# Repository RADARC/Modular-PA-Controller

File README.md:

# Modular-PA-Controller
Controller for High Power RF Power Amplifiers based Raspberry Pi Pico

Reading and District Amateur Radio Club(RADARC) are working together on a number of collaborative construction projects. This one is to design and build a Modular PA controller for High Power (1kW plus) semiconductor Power amplifiers.
This prototype implementation is targetted on the High Power HF PA Modules from [W6PQL](https://www.w6pql.com/) :

* [Kilowatt PA](https://www.w6pql.com/1_kw_sspa_for_1_8-54_mhz.htm)
* [LPF Filter](https://www.w6pql.com/a_1.5kw_lpf_for_160-6m.htm)
* [Directional Coupler](https://www.w6pql.com/1_8_to_54_mhz_dual_coupler.htm)

## Objectives:
<ul>
<li><strong>Protection</strong></li>
<ul>
<li>Protection of user and premises</li>
<li>Protection of Power Amplifier</li>
<li>Protection of connected equipment</li>
</ul>
<li><strong>Automatic Operation and Sequencing</strong>
<ul>
<li>Monitoring of Power Amplifier operational state</li>
<li>Control of operational components of Power Amplifier</li>
<li>Detection of state of connected equipment</li>
<li>Sequencing and crystal controlled timing of sequencing</li>
</ul>
<li><strong>Power Supplies</strong></li>
<ul>
<li>Low voltage power supplies derived from High Voltage PA supply</li>
<li>Variable Vgg Bias voltage supply</li>
</ul>
<li><strong> External control and Monitoring</strong></li>
<ul>
<li>LCD Display</li>
<li>USB</li>
<li>TTL Serial</li>
<li>Wifi and Bluetooth</li>

</ul>
</ul>

## Specification
<ul>
<li>Processor: Raspberry Pi Pico</li>
<li>Maximum input Voltage: 72V DC</li>
<li>Maximum switched PA current: 50A</li>
<li>Vgg bias output range: 1.4V to 4.7V</li>
<li>Number of PWM and RPM monitored fans(5V or 12V): 3</li>
<li>Number of voltage controlled fans: 1</li>
<li>Number of directional coupler inputs: 3</li>
<li>Analogue meter outputs: 2
<li>Transceiver ALC output: -12V to +12V</li>
<li>Transceiver digital SEND in/out Ports: 1</li>
<li>OLED control ports: 1</li>
<li>Rotary Encoders: 2</li>
<li>OLED control ports: 1</li>
<li>Input frequency measurement range: 100kHz to 50MHz</li>
<li>Input Power detection: 10dBm to 50dBm</li>
<li>Maximum input Power Tx/RX switching: 50dBm</li>
<li>Output TX/RX relay drivers(5V or 12V): 2</li>
<li>Output LPF relay drivers(%V or 12V): 6</li>
<li>I2C ports: 1</li>
<li>TTLserial ports: 1</li>                                                                                               
</ul>

## Hardware Implementation

The Modular PA Controller Is built around four PCB assemblies:

### Power Supply and Control Board
This board manages the high DC voltage (up to 72V) part of the PA controller. It provides switching of the DC supply up to 50A, also current monitoring and Voltage monitoring. The DC supply switching uses a watchdog an requires the processor to signal the switch every 500uS to keep the power on.
It derives two lower voltage power supplies at 12V 2A and 5V 1A. The 3.3V logic supply for th PA controller is provided by the regulator on the Pi Pico on the processor board.To control the Vgg Bias to the Power Amplifier Modules the board provides either a switched 12V supply to a regulator on the Power Amplifier Board, and also a variable voltage software controlled DC output.
All control and monitoring is via I2C control from the Processor Board.

[Kicad Files](./Kicad/PA_Power_V1/)

### Processor and Interface Board
This board contains the Raspberry Pi Pico microcontroller module. The module alo provides the 3.3V logic supply and the USB interface. Pi Pico modules with Bluetooth and Wi-fi may be used, also the higher performance RP2350 version.

[Pi Pico Data sheet](https://datasheets.raspberrypi.com/pico/pico-datasheet.pdf)

The board has two I2C buses. The internal bus connects to the on board ADC and DAC devices. The external I2C bus connects to the Power Supply and Control board(s), the Relay Driver board(s), LM75 temperature sensors, I2C OLED display, etc.

The board has an input TX/RX relay to bypass the Power Amplifier Modules as required.

### Relay Driver Board

### RF screen

## Software Implementation

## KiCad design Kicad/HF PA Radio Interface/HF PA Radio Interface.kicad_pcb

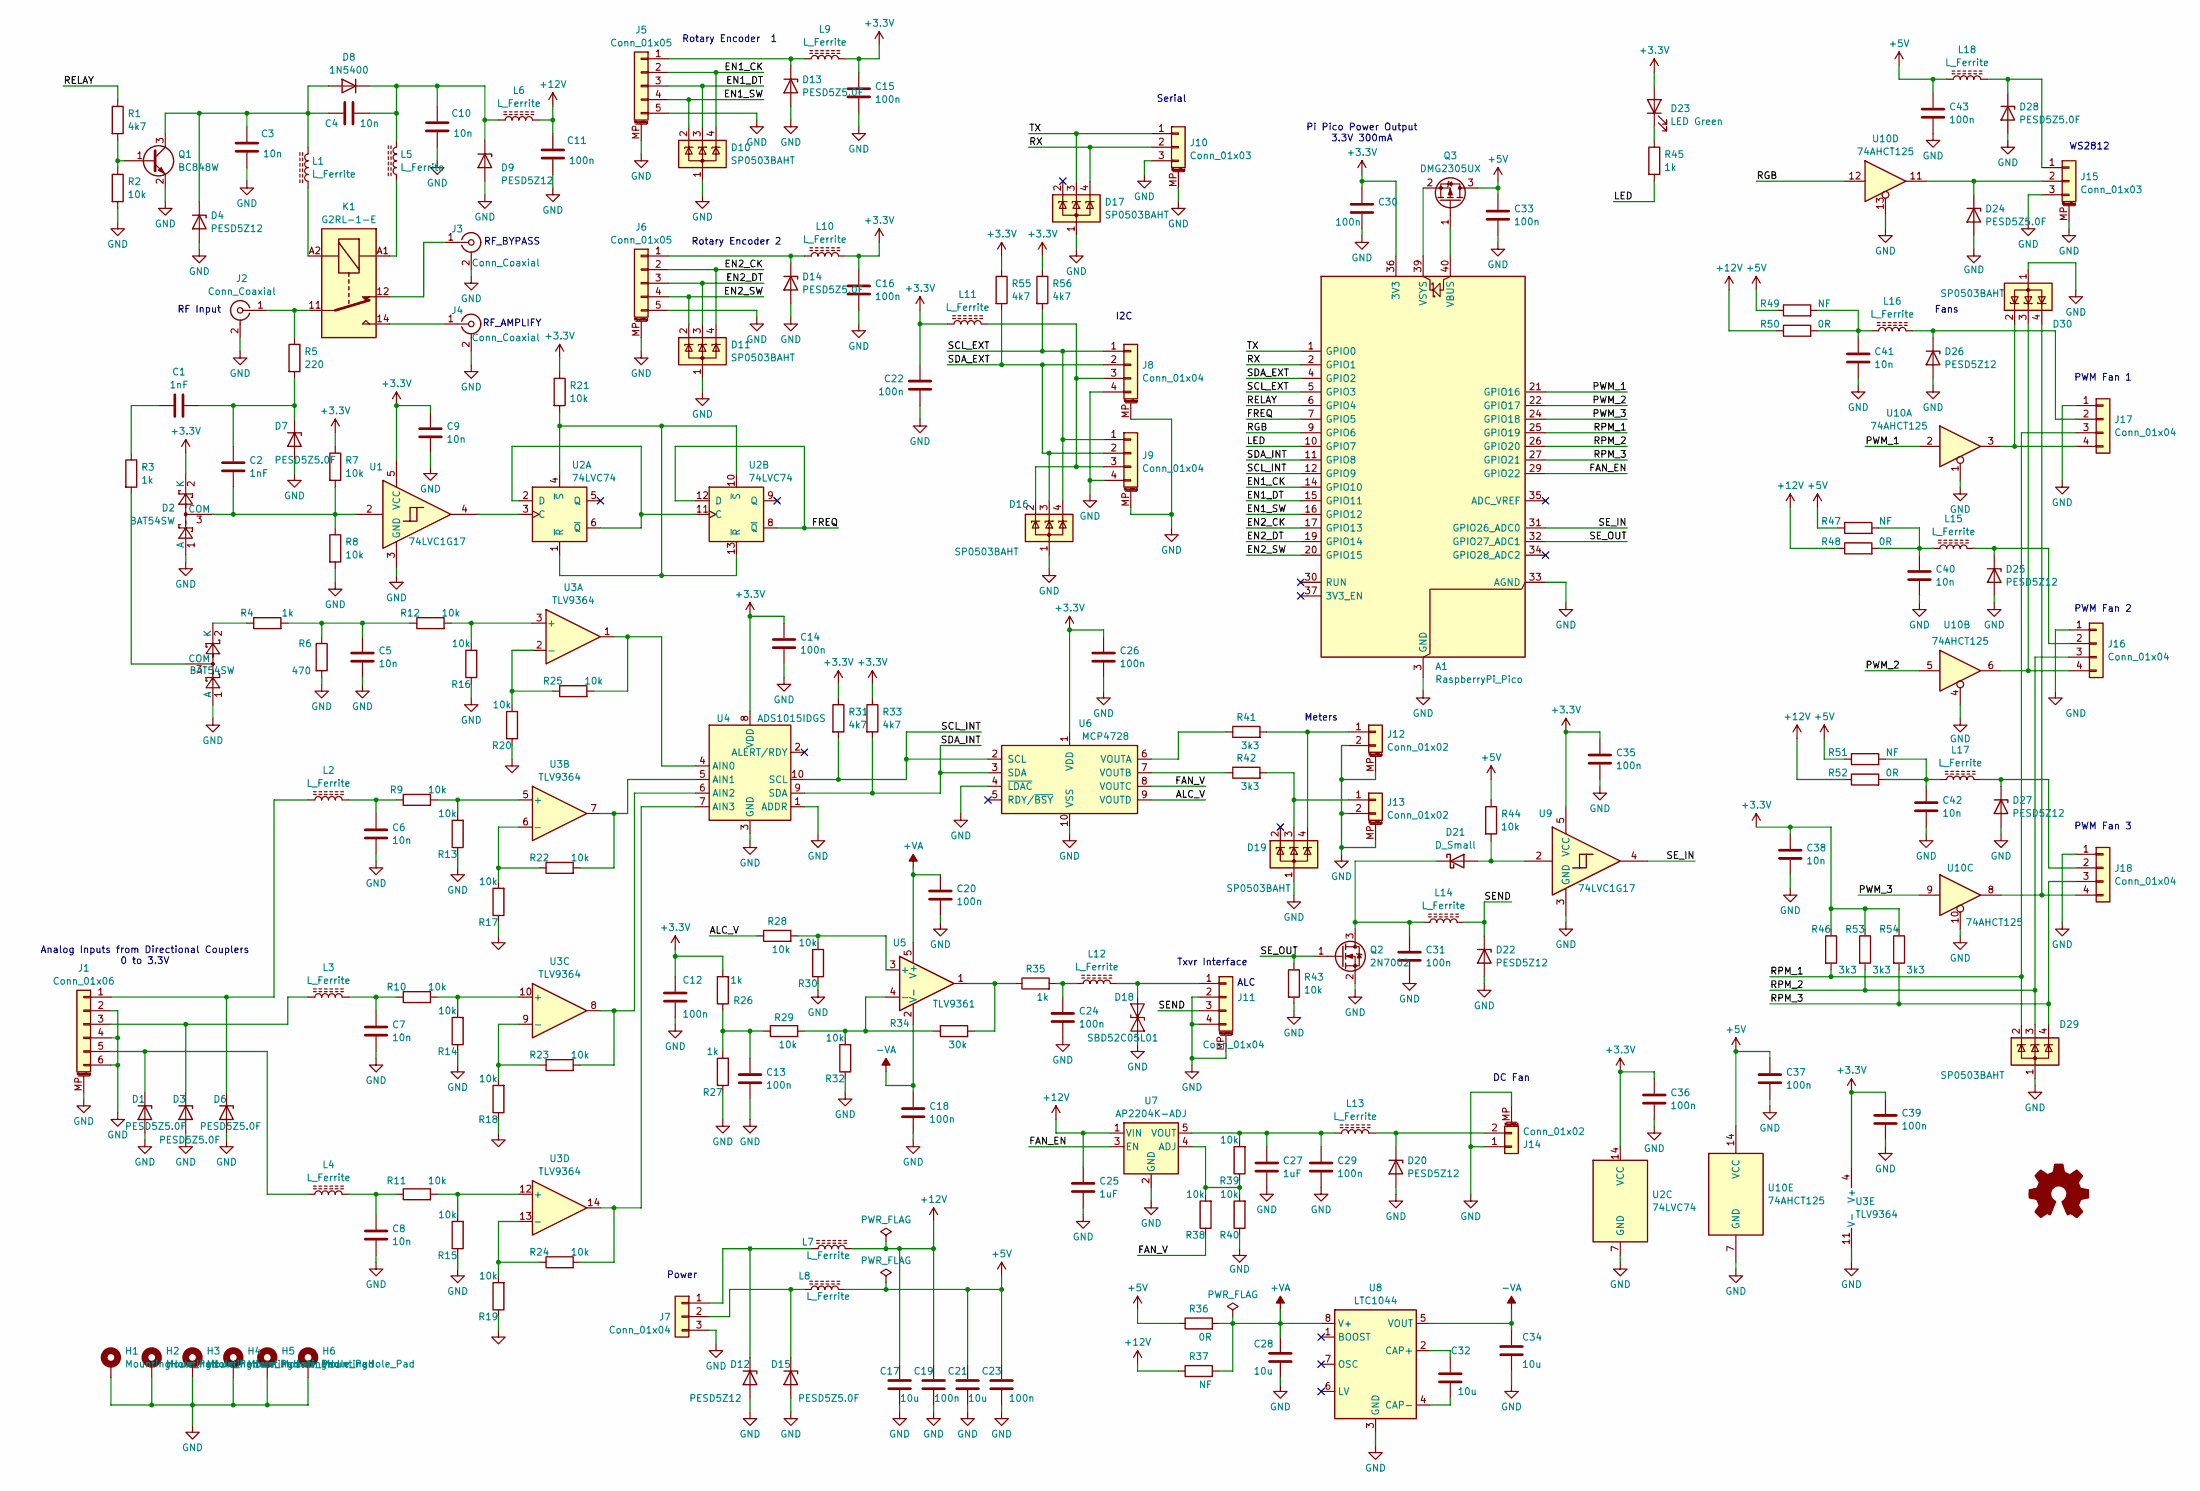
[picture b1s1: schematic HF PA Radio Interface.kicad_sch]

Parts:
A1: RaspberryPi_Pico; RPi_Pico_SMD_TH
C1, C2: 1nF; C_0603_1608Metric
C3, C4, C5, C6, C7, C8, C9, C10, C38, C40, C41, C42: 10n; C_0603_1608Metric
C11, C12, C13, C14, C15, C16, C18, C19, C20, C22, C23, C24, C26, C29, C30, C31, C33, C35, C36, C37, C39, C43: 100n; C_0603_1608Metric
C17, C21: 10u; C_0805_2012Metric
C25, C27: 1uF; C_0603_1608Metric
C28, C32, C34: 10u; C_0603_1608Metric
D1, D3, D6, D7, D13, D14, D15, D24, D28: PESD5Z5.0F; D_SOD-523
D2, D5: BAT54SW; SOT-323_SC-70
D4, D9, D12, D20, D22, D25, D26, D27: PESD5Z12; D_SOD-523
D8: 1N5400; D_SOD-123
D10, D11, D16, D17, D19, D29, D30: SP0503BAHT; SOT-143
D18: SBD52C05L01; D_SOD-523
D21: D_Small; D_SOD-323
D23: LED Green; LED_0603_1608Metric
H1, H2, H3, H4, H5, H6: MountingHole_Pad; MountingHole_3.2mm_M3_DIN965_Pad
J1: Conn_01x06; JST_PH_S6B-PH-SM4-TB_1x06-1MP_P2.00mm_Horizontal
J2, J3, J4: Conn_Coaxial; SMA_Samtec_SMA-J-P-X-ST-EM1_EdgeMount
J5, J6: Conn_01x05; JST_PH_B5B-PH-SM4-TB_1x05-1MP_P2.00mm_Vertical
J7: Conn_01x04; JST_XH_S3B-XH-A_1x03_P2.50mm_Horizontal
J8, J9, J11: Conn_01x04; JST_PH_B4B-PH-SM4-TB_1x04-1MP_P2.00mm_Vertical
J10: Conn_01x03; JST_PH_B3B-PH-SM4-TB_1x03-1MP_P2.00mm_Vertical
J12, J13: Conn_01x02; JST_PH_B2B-PH-SM4-TB_1x02-1MP_P2.00mm_Vertical
J14: Conn_01x02; JST_PH_S2B-PH-SM4-TB_1x02-1MP_P2.00mm_Horizontal
J15: Conn_01x03; JST_PH_S3B-PH-SM4-TB_1x03-1MP_P2.00mm_Horizontal
J16, J17, J18: Conn_01x04; KF2510-4AW_3+1P
K1: G2RL-1-E; Relay_SPDT_Omron_G2RL-1-E
L1, L2, L3, L4, L5, L6, L7, L8, L9, L10, L11, L12, L13, L14, L15, L16, L17, L18: L_Ferrite; L_0603_1608Metric
Q1: BC848W; SOT-323_SC-70
Q2: 2N7002; SOT-23
Q3: DMG2305UX; SOT-23
R1, R31, R33, R55, R56: 4k7; R_0603_1608Metric
R2, R7, R8, R9, R10, R11, R12, R13, R14, R15, R16, R17, R18, R19, R20, R21, R22, R23, R24, R25, R28, R29, R30, R32, R38, R39, R40, R43, R44: 10k; R_0603_1608Metric
R3, R4, R26, R27, R35, R45: 1k; R_0603_1608Metric
R5: 220; R_0603_1608Metric
R6: 470; R_0603_1608Metric
R34: 30k; R_0603_1608Metric
R36, R48, R50, R52: 0R; R_0603_1608Metric
R37, R47, R49, R51: NF; R_0603_1608Metric
R41, R42, R46, R53, R54: 3k3; R_0603_1608Metric
SYM1: Logo_Open_Hardware_Small; OSHW-Logo2_7.3x6mm_SilkScreen
U1, U9: 74LVC1G17; SOT-353_SC-70-5
U2: 74LVC74; SOIC-14_3.9x8.7mm_P1.27mm
U3: TLV9364; SOIC-14_3.9x8.7mm_P1.27mm
U4: ADS1015IDGS; TSSOP-10_3x3mm_P0.5mm
U5: TLV9361; SOT-23-5
U6: MCP4728; MSOP-10_3x3mm_P0.5mm
U7: AP2204K-ADJ; SOT-23-5
U8: LTC1044; SOIC-8_5.23x5.23mm_P1.27mm
U10: 74AHCT125; TSSOP-14_4.4x5mm_P0.65mm

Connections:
+3.3V: A1.36 (3V3), C9.1, C12.1, C14.1, C15.1, C16.1, C22.1, C26.1, C30.1, C35.1, C36.1, C38.1, C39.1, D2.2 (K), D23.2 (A), L9.2, L10.2, L11.2, R7.1, R21.1, R26.2, R31.1, R33.1, R46.1, R53.1, R54.1, R55.1, R56.1, U1.5 (VCC), U2.14 (VCC), U3.4 (V+), U4.8 (VDD), U6.1 (VDD), U9.5 (VCC)
+5V: C21.1, C23.1, C33.1, C37.1, C43.1, L8.2, L18.1, Q3.3 (D), R36.1, R44.1, R47.1, R49.1, R51.1, U10.14 (VCC)
+12V: C11.1, C17.1, C19.1, C25.1, L6.2, L7.2, R37.1, R48.1, R50.1, R52.1, U7.1 (VIN)
+VA: C20.1, C28.1, R36.2, R37.2, U5.5 (V+), U8.8 (V+)
-VA: C18.1, C34.1, U5.2 (V-), U8.5 (VOUT)
/ALC_V: R28.1, U6.9 (VOUTD)
/EN1_CK: A1.14 (GPIO10), D10.4 (K), J5.2
/EN1_DT: A1.15 (GPIO11), D10.3 (K), J5.3
/EN1_SW: A1.16 (GPIO12), D10.2 (K), J5.4
/EN2_CK: A1.17 (GPIO13), D11.4 (K), J6.2
/EN2_DT: A1.19 (GPIO14), D11.3 (K), J6.3
/EN2_SW: A1.20 (GPIO15), D11.2 (K), J6.4
/FAN_EN: A1.29 (GPIO22), U7.3 (EN)
/FAN_V: R38.1, U6.8 (VOUTC)
/FREQ: A1.7 (GPIO5), U2.8 (~Q), U2.12 (D)
/LED: A1.10 (GPIO7), R45.2
/PWM_1: A1.21 (GPIO16), U10.2
/PWM_2: A1.22 (GPIO17), U10.5
/PWM_3: A1.24 (GPIO18), U10.9
/RELAY: A1.6 (GPIO4), R1.1
/RGB: A1.9 (GPIO6), U10.12
/RPM_1: A1.25 (GPIO19), D29.2 (K), J17.3, R46.2
/RPM_2: A1.26 (GPIO20), D29.3 (K), J16.3, R53.2
/RPM_3: A1.27 (GPIO21), D29.4 (K), J18.3, R54.2
/RX: A1.2 (GPIO1), D17.4 (K), J10.2
/SCL_EXT: A1.5 (GPIO3), D16.4 (K), J8.1, J9.1, R56.2
/SCL_INT: A1.12 (GPIO9), R31.2, U4.10 (SCL), U6.2 (SCL)
/SDA_EXT: A1.4 (GPIO2), D16.3 (K), J8.2, J9.2, R55.2
/SDA_INT: A1.11 (GPIO8), R33.2, U4.9 (SDA), U6.3 (SDA)
/SEND: D22.1 (K), J11.3, L14.2
/SE_IN: A1.31 (GPIO26_ADC0), U9.4
/SE_OUT: A1.32 (GPIO27_ADC1), Q2.1 (G), R43.1
/TX: A1.1 (GPIO0), D17.3 (K), J10.1
GND: A1.3 (GND), A1.8 (GND), A1.13 (GND), A1.18 (GND), A1.23 (GND), A1.28 (GND), A1.33 (AGND), A1.38 (GND), C3.2, C5.2, C6.2, C7.2, C8.2, C9.2, C10.2, C11.2, C12.2, C13.2, C14.2, C15.2, C16.2, C17.2, C18.2, C19.2, C20.2, C21.2, C22.2, C23.2, C24.2, C25.2, C26.2, C27.2, C28.2, C29.2, C30.2, C31.2, C33.2, C34.2, C35.2, C36.2, C37.2, C38.2, C39.2, C40.2, C41.2, C42.2, C43.2, D1.2 (A), D2.1 (A), D3.2 (A), D4.2 (A), D5.1 (A), D6.2 (A), D7.2 (A), D9.2 (A), D10.1 (A), D11.1 (A), D12.2 (A), D13.2 (A), D14.2 (A), D15.2 (A), D16.1 (A), D17.1 (A), D18.1 (A1), D19.1 (A), D20.2 (A), D22.2 (A), D24.2 (A), D25.2 (A), D26.2 (A), D27.2 (A), D28.2 (A), D29.1 (A), D30.1 (A), H1.1, H2.1, H3.1, H4.1, H5.1, H6.1, J1.2, J1.4, J1.6, J1.MP (MountPin), J2.2 (Ext), J3.2 (Ext), J4.2 (Ext), J5.5, J5.MP (MountPin), J6.5, J6.MP (MountPin), J7.3, J8.4, J8.MP (MountPin), J9.4, J9.MP (MountPin), J10.3, J10.MP (MountPin), J11.2, J11.4, J11.MP (MountPin), J12.2, J12.MP (MountPin), J13.2, J13.MP (MountPin), J14.1, J14.MP (MountPin), J15.3, J15.MP (MountPin), J16.1, J17.1, J18.1, Q1.2 (E), Q2.2 (S), R2.2, R6.2, R8.2, R13.1, R14.1, R15.1, R16.1, R17.1, R18.1, R19.1, R20.1, R27.1, R30.1, R32.1, R40.1, R43.2, U1.3 (GND), U2.7 (GND), U3.11 (V-), U4.1 (ADDR), U4.3 (GND), U6.4 (~LDAC), U6.10 (VSS), U7.2 (GND), U8.3 (GND), U9.3 (GND), U10.1, U10.4, U10.7 (GND), U10.10, U10.13
unnamed: A1.40 (VBUS), Q3.1 (G)
unnamed: A1.39 (VSYS), Q3.2 (S)
unnamed: C1.2, R3.1
unnamed: C5.1, R4.2, R6.1, R12.1
unnamed: C6.1, L2.2, R9.1
unnamed: C7.1, L3.2, R10.1
unnamed: C8.1, L4.2, R11.1
unnamed: C13.1, R26.1, R27.2, R29.1
unnamed: C24.1, L12.1, R35.2
unnamed: C40.1, L15.1, R47.2, R48.2
unnamed: C41.1, L16.1, R49.2, R50.2
unnamed: C42.1, L17.1, R51.2, R52.2
unnamed: D1.1 (K), J1.5, L4.1
unnamed: C2.2, D2.3 (COM), R7.2, R8.1, U1.2
unnamed: D3.1 (K), J1.3, L3.1
unnamed: C3.1, C4.1, D4.1 (K), D8.2 (A), L1.2, Q1.3 (C)
unnamed: D5.3 (COM), R3.2
unnamed: D5.2 (K), R4.1
unnamed: D6.1 (K), J1.1, L2.1
unnamed: C1.1, C2.1, D7.1 (K), R5.2
unnamed: C4.2, C10.1, D8.1 (K), D9.1 (K), L5.2, L6.1
unnamed: D12.1 (K), J7.1, L7.1
unnamed: D13.1 (K), J5.1, L9.1
unnamed: D14.1 (K), J6.1, L10.1
unnamed: D15.1 (K), J7.2, L8.1
unnamed: D18.2 (A2), J11.1, L12.2
unnamed: D20.1 (K), J14.2, L13.2
unnamed: D21.2 (A), R44.2, U9.2
unnamed: C31.1, D21.1 (K), L14.1, Q2.3 (D)
unnamed: D23.1 (K), R45.1
unnamed: D24.1 (K), J15.2, U10.11
unnamed: D25.1 (K), J16.2, L15.2
unnamed: D26.1 (K), J17.2, L16.2
unnamed: D27.1 (K), J18.2, L17.2
unnamed: D28.1 (K), J15.1, L18.2
unnamed: J2.1 (In), K1.11, R5.1
unnamed: J3.1 (In), K1.12
unnamed: J4.1 (In), K1.14
unnamed: D16.2 (K), J8.3, J9.3, L11.1
unnamed: D19.4 (K), J12.1, R41.2
unnamed: D19.3 (K), J13.1, R42.2
unnamed: D30.3 (K), J16.4, U10.6
unnamed: D30.2 (K), J17.4, U10.3
unnamed: D30.4 (K), J18.4, U10.8
unnamed: K1.A1, L5.1
unnamed: K1.A2, L1.1
unnamed: Q1.1 (B), R1.2, R2.1
unnamed: R34.2, R35.1, U5.1
unnamed: U1.4, U2.3 (C)
unnamed: U2.2 (D), U2.6 (~Q), U2.11 (C)
unnamed: R21.2, U2.1 (~R), U2.4 (~S), U2.10 (~S), U2.13 (~R)
unnamed: R12.2, R16.2, U3.3 (+)
unnamed: R20.2, R25.1, U3.2 (-)
unnamed: R9.2, R13.2, U3.5 (+)
unnamed: R17.2, R22.1, U3.6 (-)
unnamed: R10.2, R14.2, U3.10 (+)
unnamed: R18.2, R23.1, U3.9 (-)
unnamed: R11.2, R15.2, U3.12 (+)
unnamed: R19.2, R24.1, U3.13 (-)
unnamed: R25.2, U3.1, U4.4 (AIN0)
unnamed: R22.2, U3.7, U4.5 (AIN1)
unnamed: R23.2, U3.8, U4.6 (AIN2)
unnamed: R24.2, U3.14, U4.7 (AIN3)
unnamed: R28.2, R30.2, U5.3 (+)
unnamed: R29.2, R32.2, R34.1, U5.4 (-)
unnamed: R41.1, U6.6 (VOUTA)
unnamed: R42.1, U6.7 (VOUTB)
unnamed: R38.2, R39.1, R40.2, U7.4 (ADJ)
unnamed: C27.1, C29.1, L13.1, R39.2, U7.5 (VOUT)
unnamed: C32.1, U8.2 (CAP+)
unnamed: C32.2, U8.4 (CAP-)

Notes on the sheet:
Rotary Encoder 2
RF Input
Fans
Txvr Interface
DC Fan
PWM Fan 1
ALC
RF_BYPASS
Serial
RF_AMPLIFY
PWM Fan 3
Rotary Encoder 1
PWM Fan 2
Analog Inputs from Directional Couplers 0 to 3.3V
Power
Meters
WS2812
Pi Pico Power Output 3.3V 300mA
I2C

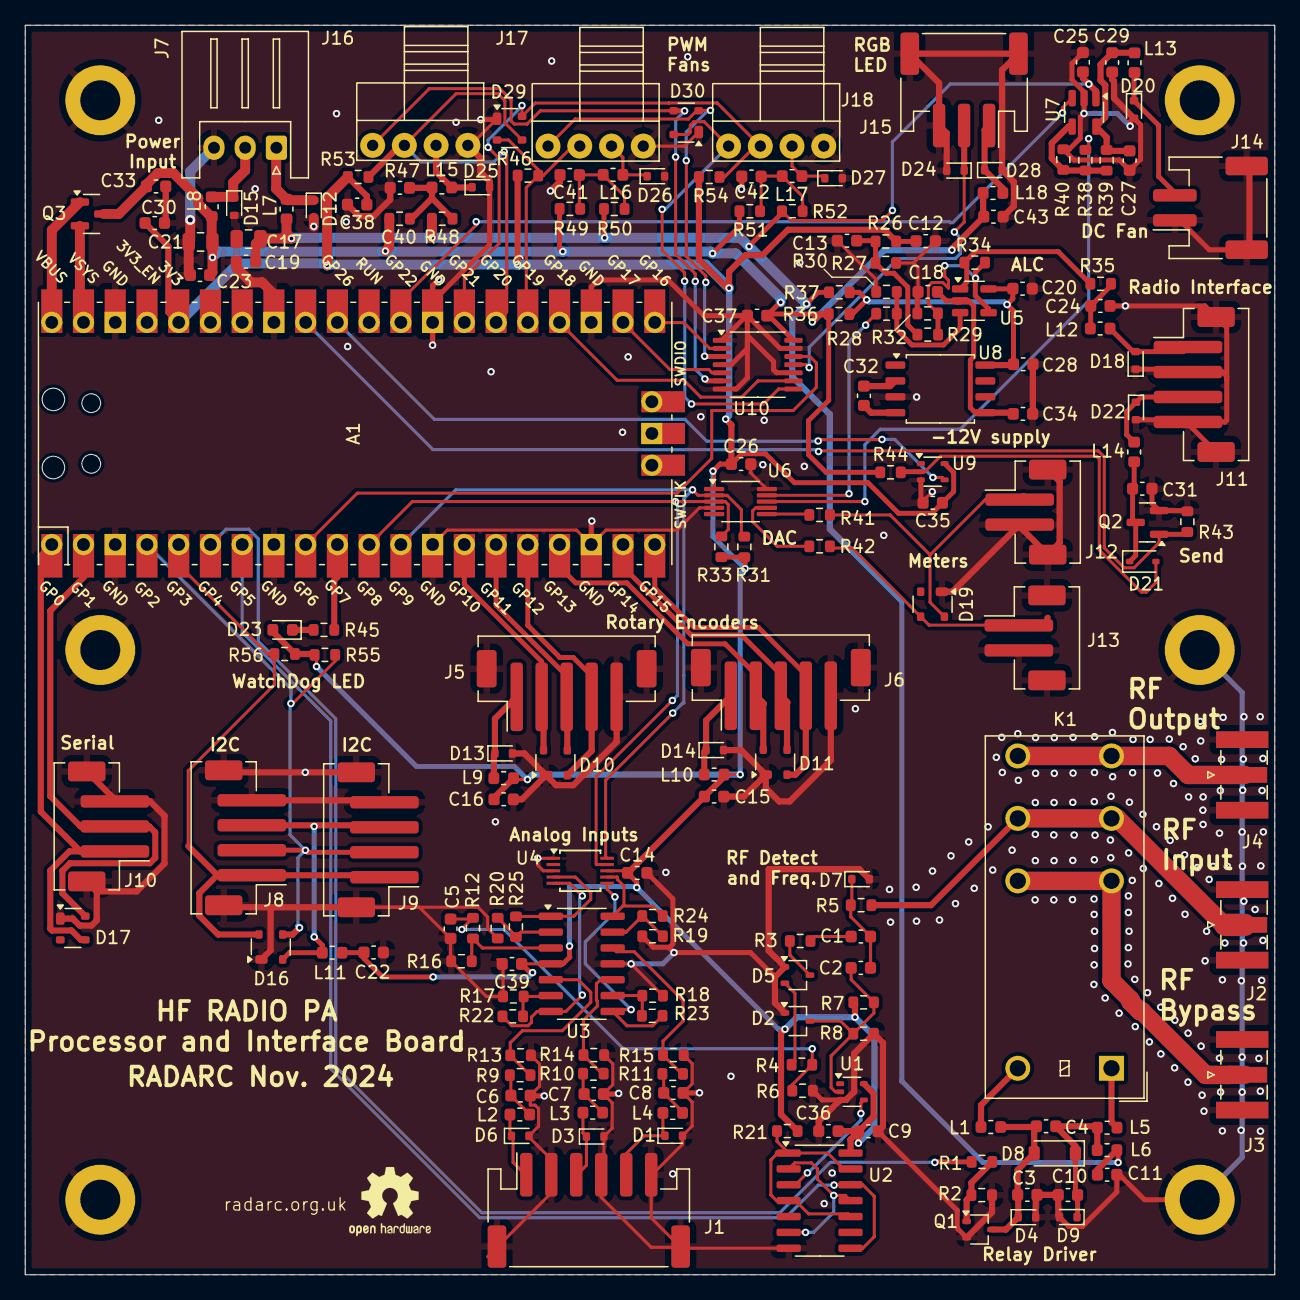
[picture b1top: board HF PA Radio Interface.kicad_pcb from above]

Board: 2 copper layers, 100.0 x 100.0 mm, 187 parts (0 on the bottom side), 105 nets.

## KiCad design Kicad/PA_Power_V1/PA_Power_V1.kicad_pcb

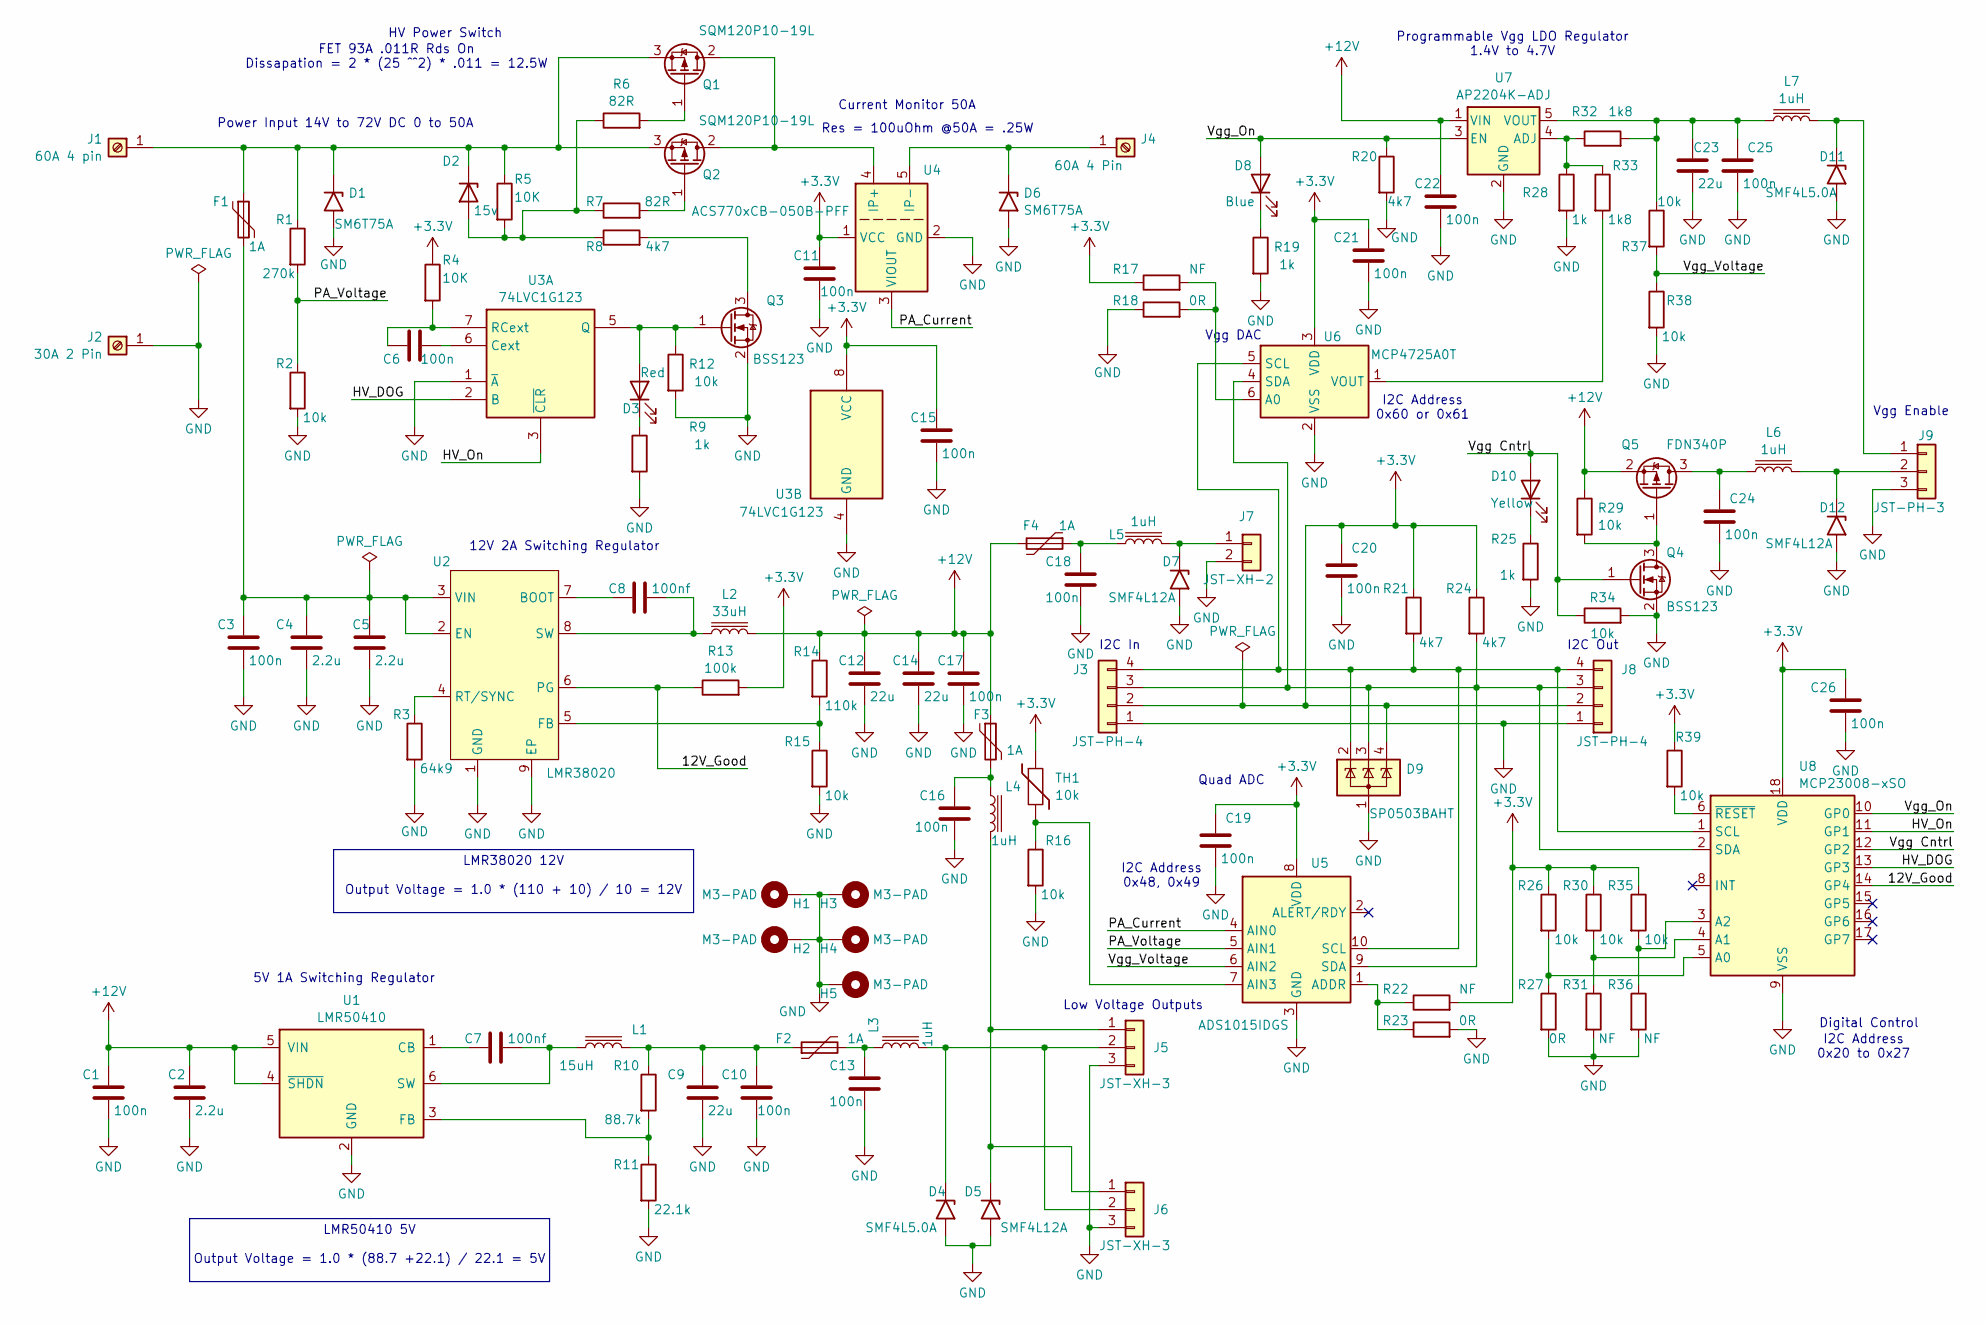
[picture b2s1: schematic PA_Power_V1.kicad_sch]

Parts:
C1, C10, C11, C13, C15, C16, C17, C18, C19, C20, C21, C22, C24, C25, C26: 100n; C_0603_1608Metric
C2: 2.2u; C_0603_1608Metric
C3, C6: 100n; C_0805_2012Metric
C4, C5: 2.2u; C_1210_3225Metric
C7, C8: 100nf; C_0603_1608Metric
C9, C12, C14: 22u; C_1210_3225Metric
C23: 22u; C_0805_2012Metric
D1, D6: SM6T75A; D_SMB
D2: 15v; Nexperia_CFP3_SOD-123W
D3: Red; LED_0603_1608Metric
D4, D11: SMF4L5.0A; D_SOD-123F
D5, D7, D12: SMF4L12A; D_SOD-123F
D8: Blue; LED_0603_1608Metric
D9: SP0503BAHT; SOT-143
D10: Yellow; LED_0603_1608Metric
F1: 1A; Fuse_Schurter_UMZ250
F2, F3, F4: 1A; Fuse_1812_4532Metric
H1, H2, H3, H4, H5: M3-PAD; MountingHole_3.2mm_M3_DIN965_Pad
J1: 60A 4 pin; Fat_Power 4
J2: 30A 2 Pin; Fat_Power 2
J3, J8: JST-PH-4; JST_PH_B4B-PH-SM4-TB_1x04-1MP_P2.00mm_Vertical
J4: 60A 4 Pin; Fat_Power 4
J5, J6: JST-XH-3; JST_XH_S3B-XH-A_1x03_P2.50mm_Horizontal
J7: JST-XH-2; JST_XH_S2B-XH-A_1x02_P2.50mm_Horizontal
J9: JST-PH-3; JST_PH_S3B-PH-SM4-TB_1x03-1MP_P2.00mm_Horizontal
L1: 15uH; L_Wuerth_MAPI-4030
L2: 33uH; L_Coilcraft_MSS1210-XXX
L3, L4, L5, L6, L7: 1uH; L_0805_2012Metric
Q1, Q2: SQM120P10-19L; TO263_Heatsink_301
Q3, Q4: BSS123; SOT-23
Q5: FDN340P; SOT-23
R1: 270k; R_0603_1608Metric
R2, R12, R15, R16, R26, R29, R30, R34, R35, R37, R38, R39: 10k; R_0603_1608Metric
R3: 64k9; R_0603_1608Metric
R4, R5: 10K; R_0603_1608Metric
R6, R7: 82R; R_0603_1608Metric
R8, R20, R21, R24: 4k7; R_0603_1608Metric
R9, R19, R25, R28: 1k; R_0603_1608Metric
R10: 88.7k; R_0603_1608Metric
R11: 22.1k; R_0603_1608Metric
R13: 100k; R_0603_1608Metric
R14: 110k; R_0603_1608Metric
R17, R22, R31, R36: NF; R_0603_1608Metric
R18, R23, R27: 0R; R_0603_1608Metric
R32, R33: 1k8; R_0603_1608Metric
TH1: 10k; R_0603_1608Metric
U1: LMR50410; SOT-23-6
U2: LMR38020; lmr38012
U3: 74LVC1G123; SSOP-8_2.95x2.8mm_P0.65mm
U4: ACS770xCB-050B-PFF; Allegro_CB_PFF
U5: ADS1015IDGS; VSSOP-10_3x3mm_P0.5mm
U6: MCP4725A0T; SOT-23-6
U7: AP2204K-ADJ; SOT-23-5
U8: MCP23008-xSO; SOIC-18W_7.5x11.6mm_P1.27mm

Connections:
+3.3V: C11.1, C15.1, C19.1, C20.1, C21.1, C26.1, D9.4 (K), J3.2, J8.2, R4.1, R13.2, R17.1, R21.1, R22.2, R24.1, R26.1, R30.1, R35.1, R39.1, TH1.1, U3.8 (VCC), U4.1 (VCC), U5.8 (VDD), U6.3 (VDD), U8.18 (VDD)
+12V: C1.1, C2.1, C12.1, C14.1, C17.1, C22.1, F3.1, F4.2, L2.2, Q5.2 (S), R14.1, R29.1, U1.4 (~SHDN), U1.5 (VIN), U7.1 (VIN)
/12V_Good: R13.1, U2.6 (PG), U8.14 (GP4)
/HV_DOG: U3.2 (B), U8.13 (GP3)
/HV_On: U3.3 (~CLR), U8.11 (GP1)
/PA_Current: U4.3 (VIOUT), U5.4 (AIN0)
/PA_Voltage: R1.2, R2.1, U5.5 (AIN1)
/Vgg Cntrl: D10.2 (A), Q4.1 (G), R34.1, U8.12 (GP2)
/Vgg_On: D8.2 (A), R20.1, U7.3 (EN), U8.10 (GP0)
/Vgg_Voltage: R37.2, R38.1, U5.6 (AIN2)
GND: C1.2, C2.2, C3.2, C4.2, C5.2, C9.2, C10.2, C11.2, C12.2, C13.2, C14.2, C15.2, C16.2, C17.2, C18.2, C19.2, C20.2, C21.2, C22.2, C23.2, C24.2, C25.2, C26.2, D1.2 (A2), D4.2 (A2), D5.2 (A2), D6.2 (A2), D7.2 (A2), D9.1 (A), D11.2 (A2), D12.2 (A2), H1.1, H2.1, H3.1, H4.1, H5.1, J2.1, J3.1, J5.3, J6.3, J7.2, J8.1, J9.3, Q3.2 (S), Q4.2 (S), R2.2, R3.2, R9.2, R11.2, R12.2, R15.2, R16.2, R18.1, R19.2, R20.2, R23.2, R25.2, R27.2, R28.2, R31.2, R34.2, R36.2, R38.2, U1.2 (GND), U2.1 (GND), U2.9 (EP), U3.1 (~A), U3.4 (GND), U4.2 (GND), U5.3 (GND), U6.2 (VSS), U7.2 (GND), U8.9 (VSS)
unnamed: C9.1, C10.1, F2.1, L1.2, R10.1
unnamed: C13.1, F2.2, L3.1
unnamed: C16.1, F3.2, L4.1
unnamed: C18.1, F4.1, L5.1
unnamed: D1.1 (A1), D2.1 (K), F1.1, J1.1, Q1.3 (S), Q2.3 (S), R1.1, R5.1
unnamed: D2.2 (A), R5.2, R6.1, R7.1, R8.1
unnamed: D3.2 (A), Q3.1 (G), R12.1, U3.5 (Q)
unnamed: D3.1 (K), R9.1
unnamed: D4.1 (A1), J5.2, J6.2, L3.2
unnamed: D5.1 (A1), J5.1, J6.1, L4.2
unnamed: D6.1 (A1), J4.1, U4.5 (IP-)
unnamed: D7.1 (A1), J7.1, L5.2
unnamed: D8.1 (K), R19.1
unnamed: D10.1 (K), R25.1
unnamed: D11.1 (A1), J9.1, L7.2
unnamed: D12.1 (A1), J9.2, L6.2
unnamed: D9.3 (K), J3.3, J8.3, R24.2, U5.9 (SDA), U6.4 (SDA), U8.2 (SDA)
unnamed: D9.2 (K), J3.4, J8.4, R21.2, U5.10 (SCL), U6.5 (SCL), U8.1 (SCL)
unnamed: Q1.2 (D), Q2.2 (D), U4.4 (IP+)
unnamed: Q1.1 (G), R6.2
unnamed: Q2.1 (G), R7.2
unnamed: Q3.3 (D), R8.2
unnamed: Q4.3 (D), Q5.1 (G), R29.2
unnamed: C24.1, L6.1, Q5.3 (D)
unnamed: C7.1, U1.1 (CB)
unnamed: R10.2, R11.1, U1.3 (FB)
unnamed: C7.2, L1.1, U1.6 (SW)
unnamed: C8.1, U2.7 (BOOT)
unnamed: C3.1, C4.1, C5.1, F1.2, U2.2 (EN), U2.3 (VIN)
unnamed: R14.2, R15.1, U2.5 (FB)
unnamed: R3.1, U2.4 (RT/SYNC)
unnamed: C8.2, L2.1, U2.8 (SW)
unnamed: C6.2, U3.6 (Cext)
unnamed: C6.1, R4.2, U3.7 (RCext)
unnamed: R22.1, R23.1, U5.1 (ADDR)
unnamed: R16.1, TH1.2, U5.7 (AIN3)
unnamed: R17.2, R18.2, U6.6 (A0)
unnamed: R33.2, U6.1 (VOUT)
unnamed: R28.1, R32.1, R33.1, U7.4 (ADJ)
unnamed: C23.1, C25.1, L7.1, R32.2, R37.1, U7.5 (VOUT)
unnamed: R26.2, R27.1, U8.5 (A0)
unnamed: R30.2, R31.1, U8.4 (A1)
unnamed: R35.2, R36.1, U8.3 (A2)
unnamed: R39.2, U8.6 (~RESET)

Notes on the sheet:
5V 1A Switching Regulator
Current Monitor 50A
Quad ADC
Digital Control
I2C Out
Res = 100uOhm @50A = .25W
LMR38020 12V Output Voltage = 1.0 * (110 + 10) / 10 = 12V
Low Voltage Outputs
I2C In
HV Power Switch
LMR50410 5V Output Voltage = 1.0 * (88.7 +22.1) / 22.1 = 5V
I2C Address 0x20 to 0x27
Vgg Enable
FET 93A .011R Rds On Dissapation = 2 * (25 ^^2) * .011 = 12.5W
12V 2A Switching Regulator
Vgg DAC
I2C Address 0x60 or 0x61
Power Input 14V to 72V DC 0 to 50A
I2C Address 0x48, 0x49
Programmable Vgg LDO Regulator 1.4V to 4.7V

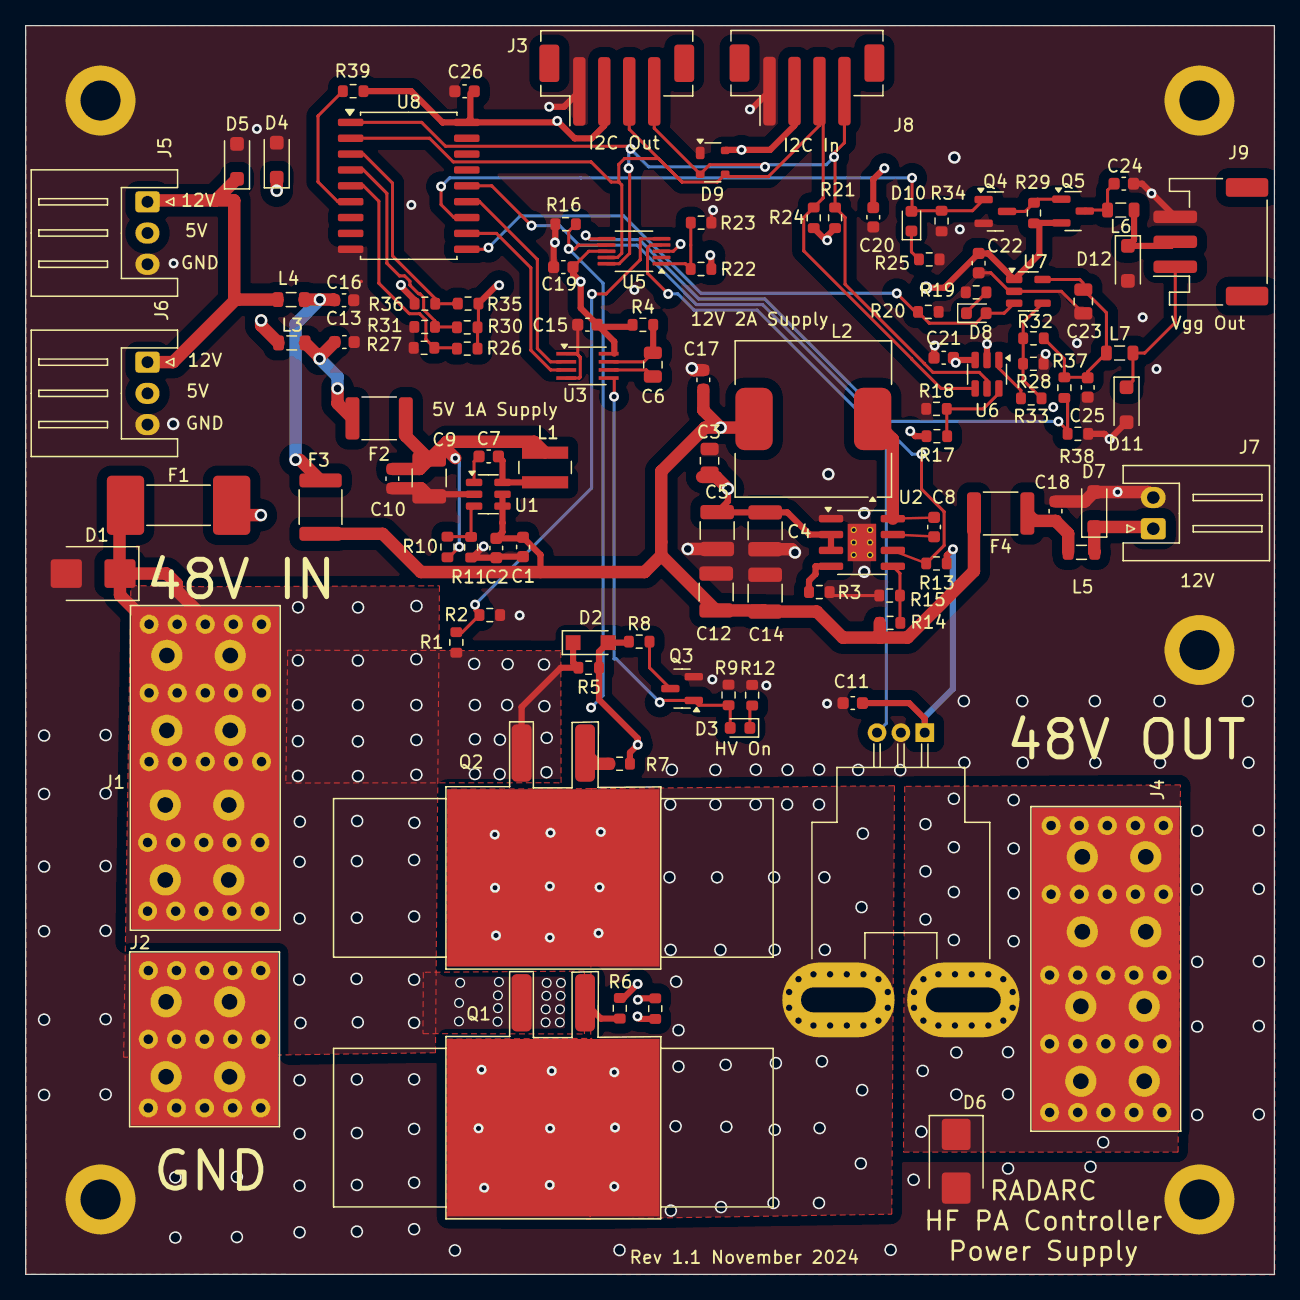
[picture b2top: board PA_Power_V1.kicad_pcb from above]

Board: 4 copper layers, 100.0 x 100.0 mm, 116 parts (0 on the bottom side), 55 nets.

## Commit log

2024-11-30 First commit of Kicad files
2025-09-26 Updates to HF PA Interface and PA Power_V1
